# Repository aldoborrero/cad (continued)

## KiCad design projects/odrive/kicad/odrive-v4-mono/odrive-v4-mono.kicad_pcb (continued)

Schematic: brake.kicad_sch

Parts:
C160: 1uF; C_0603_1608Metric
C161, C162, C168, C169, C170: 100nF; C_0603_1608Metric
C163, C164: 2.2uF 100V X7R; C_1210_3225Metric
C165: 100nF 100V X7R; C_0603_1608Metric
C166: 1nF; C_0603_1608Metric
C167, C212: 100nF 16V X7R; C_0603_1608Metric; Tolerance 10%
J13: BRAKE_EXT; TerminalBlock_Phoenix_PC-16-2-ST-10.16mm
Q50, Q51: BSC027N10NS5; Infineon_PG-TSON-8-3; MPN BSC027N10NS5ATMA1
R160: 50R/150R; R_2512_6332Metric
R161, R162: 2.2R; R_0603_1608Metric
R163: 47k; R_0603_1608Metric
R164: 2mR; R_Shunt_Vishay_WSK2512_6332Metric_T2.66mm
R165: 3.3k; R_0603_1608Metric
R166, R167: 10k; R_0603_1608Metric
R168: 1R; R_0603_1608Metric
R212: 10k; R_0603_1608Metric; Tolerance 1%
U50: UCC27517A; SOT-23-5; MPN UCC27517ADBVR
U51: INA181A2; SOT-23-6
U52: TLV3201AIDBVR; SOT-23-5; MPN TLV3201AIDBVR
U53: 74LVC1G3208; SOT-23-6; MPN SN74LVC1G3208DBVR
U54: 74LVC1G32; SOT-23-5
U55: 74LVC1G11; SOT-23-6; MPN SN74LVC1G11DBVR
U58: 74LVC1G14; SOT-23-5; MPN SN74LVC1G14DBVR

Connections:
+12V: C160.1, C161.1, U50.1 (VDD); also elsewhere on the board
/Brake Chopper/BRK_CMD: U54.4, U55.1 (A)
/Brake Chopper/BRK_DRV: R161.1, R162.1, R163.1, U50.5 (OUT)
/Brake Chopper/BRK_G0: Q50.4 (G), R161.2
/Brake Chopper/BRK_G1: Q51.4 (G), R162.2
/Brake Chopper/BRK_GATE: U50.3 (IN+), U55.4 (Y)
/Brake Chopper/BRK_OC_N: R212.1, U52.1 (OUT), U53.6, U55.6 (C)
/Brake Chopper/BRK_RESET_ACTIVE: U53.1, U58.4
/Brake Chopper/BRK_SN: R164.3, U51.4 (-)
/Brake Chopper/BRK_SNUB: C166.1, R168.2
/Brake Chopper/BRK_SP: R164.2, U51.3 (+)
/Brake Chopper/BRK_SRC: C166.2, Q50.1 (S), Q50.2 (S), Q50.3 (S), Q51.1 (S), Q51.2 (S), Q51.3 (S), R163.2, R164.1
/Brake Chopper/BRK_SW: J13.2, Q50.5 (D), Q51.5 (D), R160.2, R168.1
/Brake Chopper/BRK_TH: R165.2, R166.1, U52.3 (+)
AGND: C162.2, C167.2, R166.2, R212.2, U51.2 (GND), U51.5 (REF), U52.2 (GND); also elsewhere on the board
AVCC: C162.1, C167.1, R165.1, U51.6 (V+), U52.5 (VCC); also elsewhere on the board
BRAKE_ISENSE: U51.1, U52.4 (-); also elsewhere on the board
BRAKE_PWM: R167.1, U54.1; also elsewhere on the board
BRK_OK: U53.3, U53.4, U55.3 (B); also elsewhere on the board
DCBUS: C163.1, C164.1, C165.1, J13.1, R160.1; also elsewhere on the board
GND: C168.2, C169.2, C170.2, C212.2, R167.2, U53.2 (GND), U54.3 (GND), U55.2 (GND), U58.3 (GND); also elsewhere on the board
NRST: U58.2; also elsewhere on the board
OV_LATCH: U54.2; also elsewhere on the board
PGND: C160.2, C161.2, C163.2, C164.2, C165.2, R164.4, U50.2 (GND), U50.4 (IN-); also elsewhere on the board
VCC: C168.1, C169.1, C170.1, C212.1, U53.5 (VCC), U54.5 (VCC), U55.5 (VCC), U58.5 (VCC); also elsewhere on the board

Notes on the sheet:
MONO BRAKE FAULT-PRIORITY MEMORY BRK_OK(next) = (BRK_RESET_ACTIVE OR BRK_OK) AND BRK_OC_N. NRST LOW restores permission only while overcurrent is absent. BRK_OC_N LOW always inhibits and removes stored permission. With NRST HIGH, fault recovery alone cannot rearm. U55 independently gates the comman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

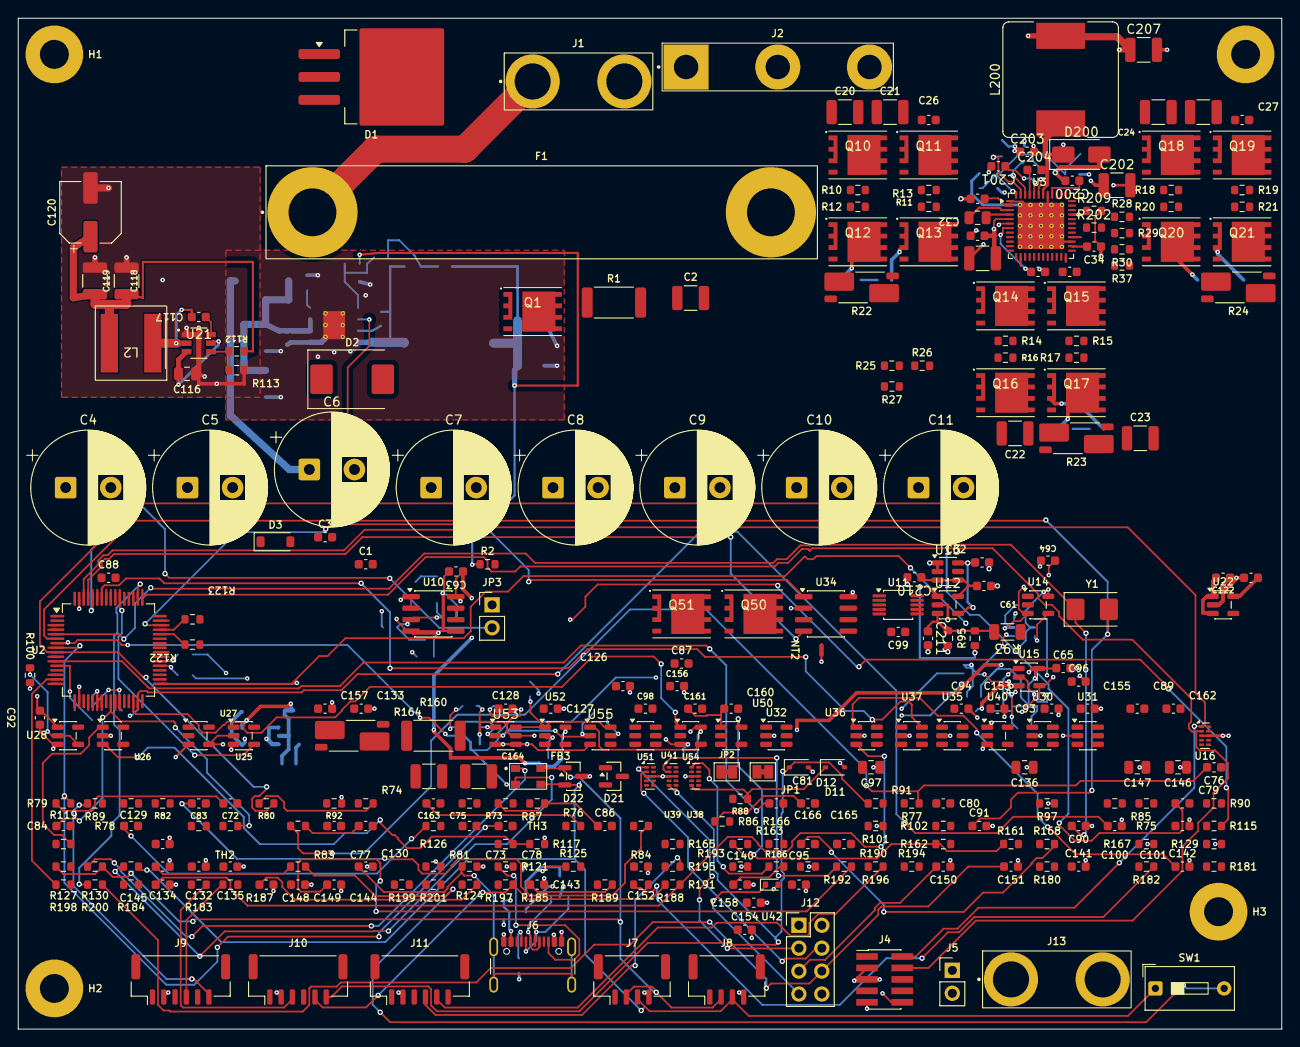
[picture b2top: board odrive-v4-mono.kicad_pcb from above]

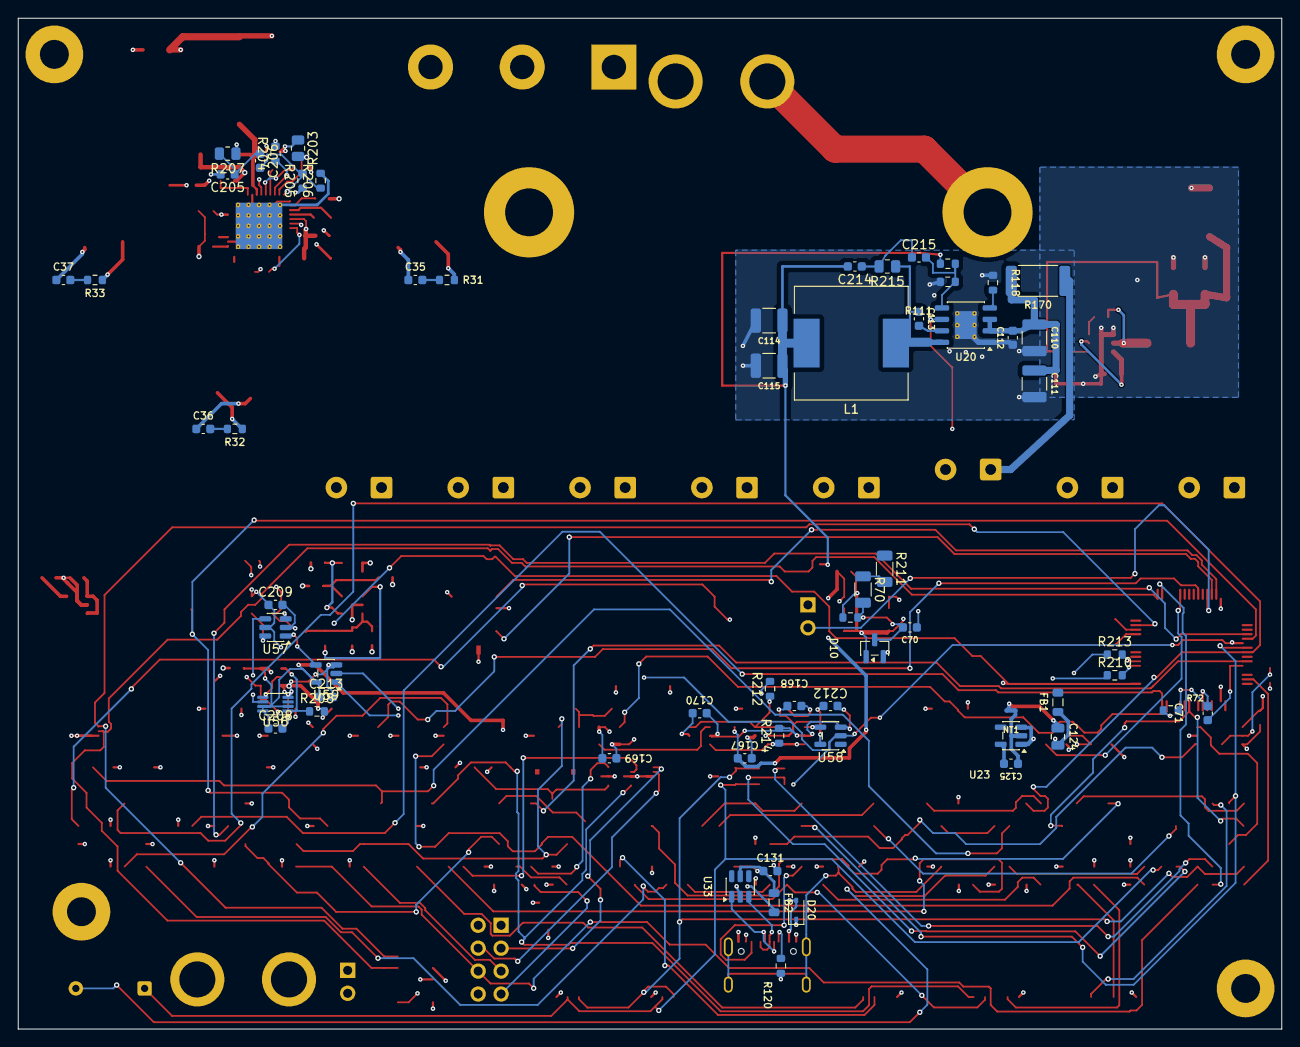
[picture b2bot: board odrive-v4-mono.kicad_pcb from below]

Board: 4 copper layers, 140.0 x 112.0 mm, 360 parts (62 on the bottom side), 206 nets.

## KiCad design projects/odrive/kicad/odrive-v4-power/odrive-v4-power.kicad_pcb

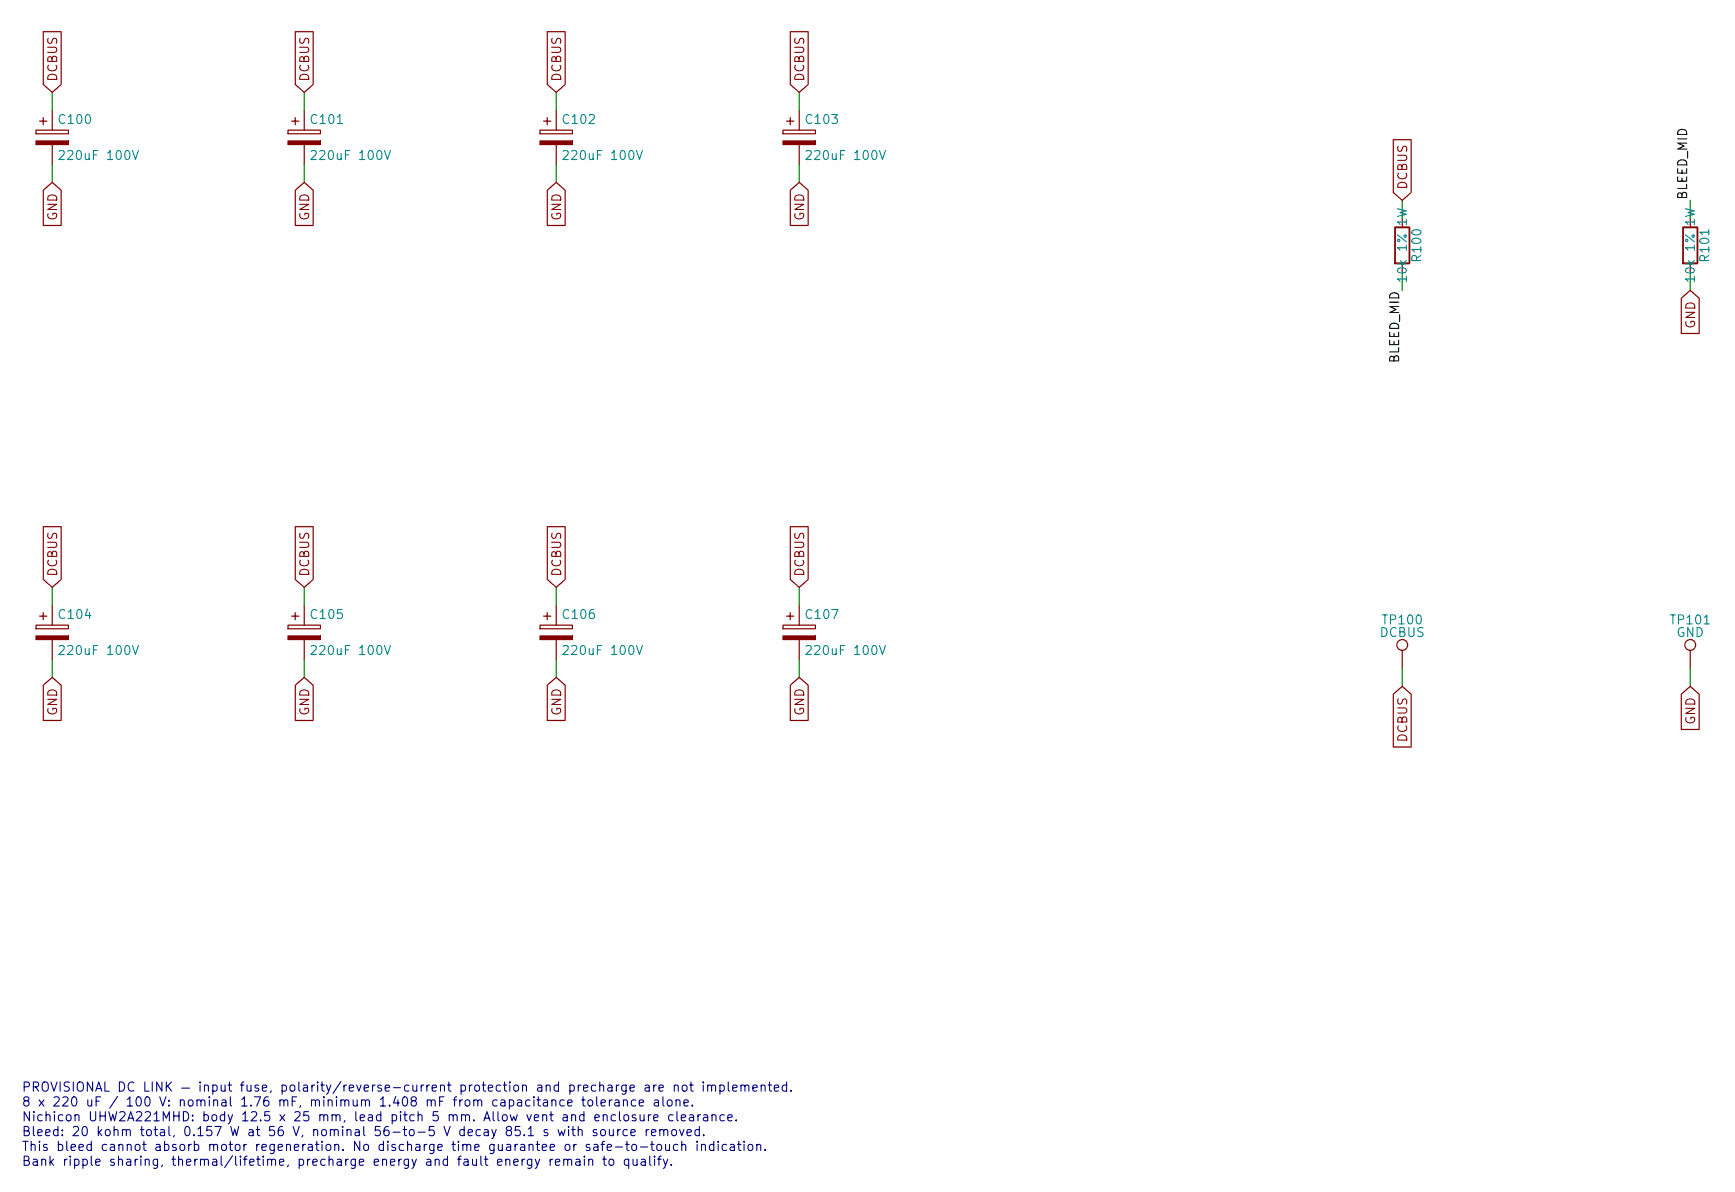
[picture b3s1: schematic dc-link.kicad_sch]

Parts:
C100, C101, C102, C103, C104, C105, C106, C107: 220uF 100V; CP_Radial_D12.5mm_P5.00mm
R100, R101: 10k 1% 1W; R_2512_6332Metric
TP100: DCBUS; TestPoint_Pad_D1.5mm
TP101: GND; TestPoint_Pad_D1.5mm

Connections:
/DC input and link/BLEED_MID: R100.2, R101.1
DCBUS: C100.1, C101.1, C102.1, C103.1, C104.1, C105.1, C106.1, C107.1, R100.1, TP100.1; also elsewhere on the board
GND: C100.2, C101.2, C102.2, C103.2, C104.2, C105.2, C106.2, C107.2, R101.2, TP101.1; also elsewhere on the board

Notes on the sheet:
PROVISIONAL DC LINK — input fuse, polarity/reverse-current protection and precharge are not implemented. 8 x 220 uF / 100 V: nominal 1.76 mF, minimum 1.408 mF from capacitance tolerance alone. Nichicon UHW2A221MHD: body 12.5 x 25 mm, lead pitch 5 mm. Allow vent and enclosure clearance. Bleed: 20 ko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

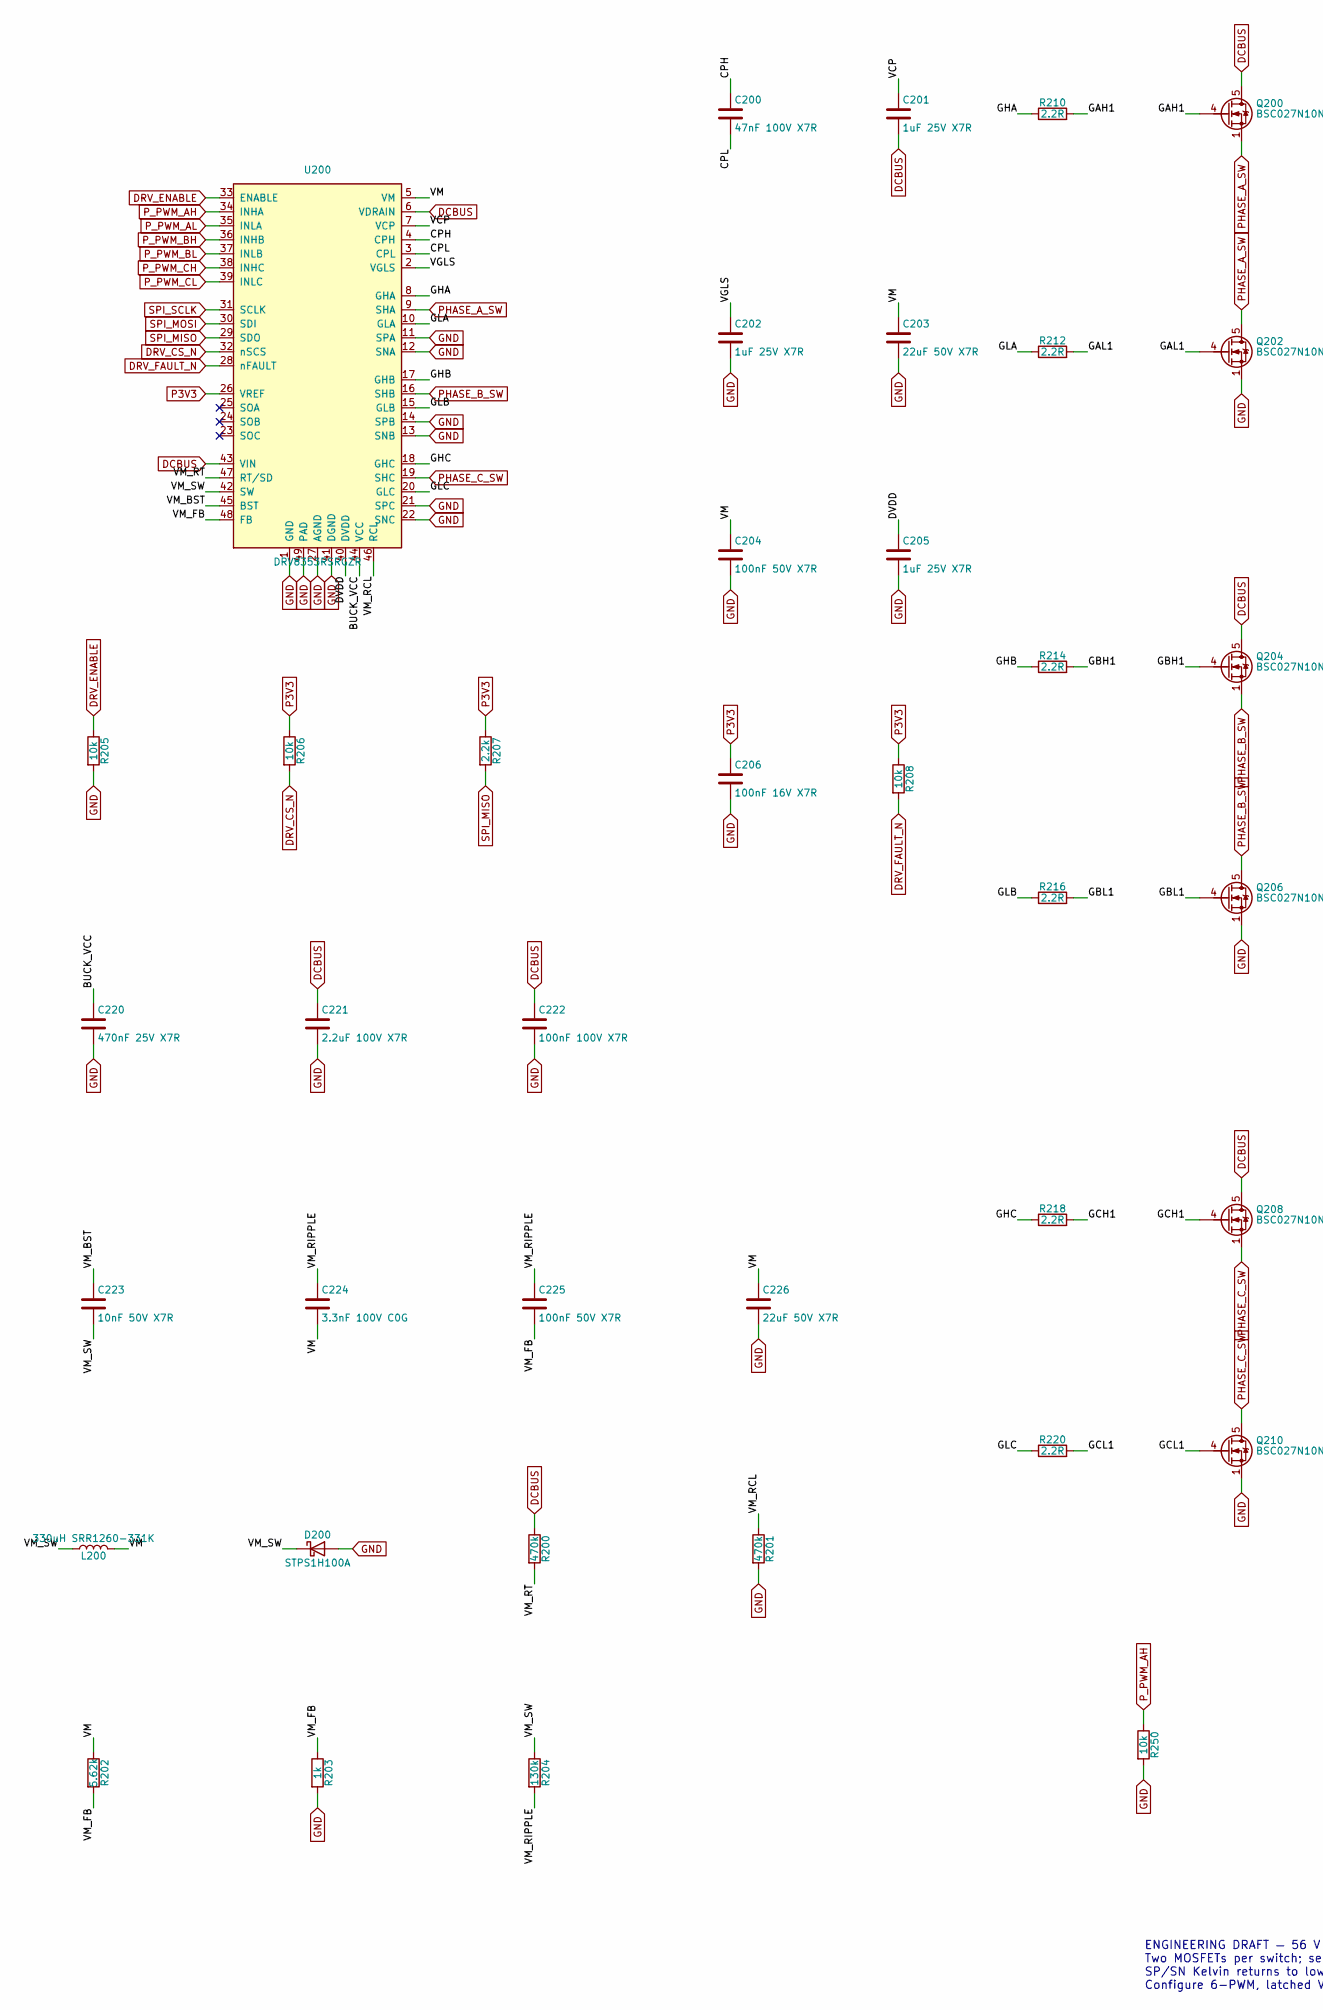
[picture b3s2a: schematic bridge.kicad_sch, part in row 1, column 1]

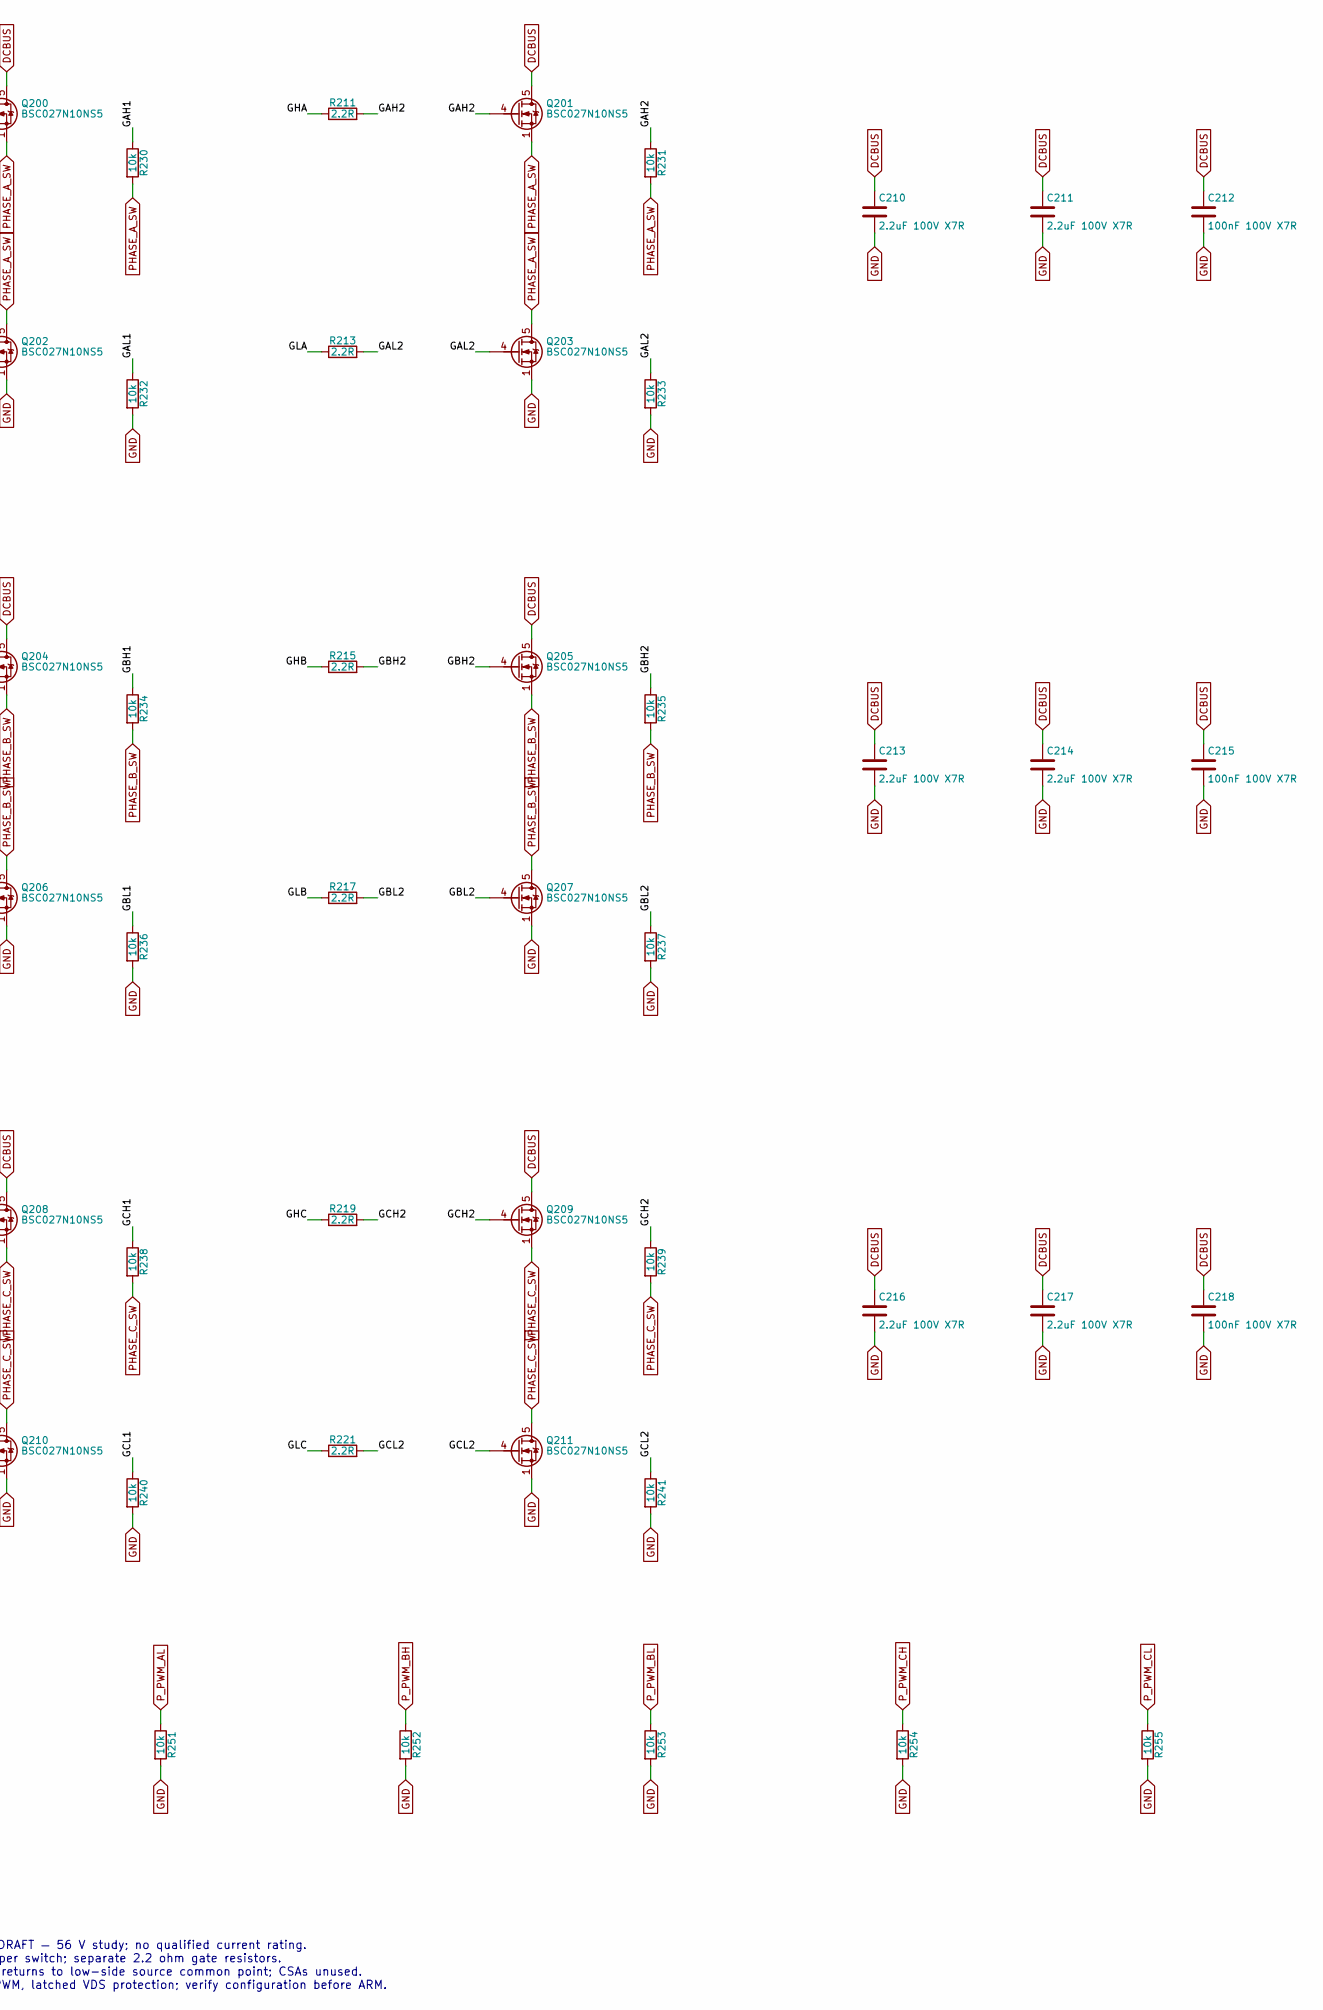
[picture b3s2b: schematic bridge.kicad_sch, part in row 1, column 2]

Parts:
C200: 47nF 100V X7R; C_0805_2012Metric
C201, C202, C205: 1uF 25V X7R; C_0603_1608Metric
C203, C226: 22uF 50V X7R; C_1210_3225Metric
C204, C225: 100nF 50V X7R; C_0603_1608Metric
C206: 100nF 16V X7R; C_0603_1608Metric
C210, C211, C213, C214, C216, C217, C221: 2.2uF 100V X7R; C_1210_3225Metric
C212, C215, C218, C222: 100nF 100V X7R; C_0603_1608Metric
C220: 470nF 25V X7R; C_0603_1608Metric
C223: 10nF 50V X7R; C_0603_1608Metric
C224: 3.3nF 100V C0G; C_0603_1608Metric
D200: STPS1H100A; D_SMA
L200: 330uH SRR1260-331K; L_Bourns_SRR1260
Q200, Q201, Q202, Q203, Q204, Q205, Q206, Q207, Q208, Q209, Q210, Q211: BSC027N10NS5; Infineon_PG-TSON-8-3
R200: 470k; R_0805_2012Metric
R201: 470k; R_0603_1608Metric
R202: 5.62k; R_0603_1608Metric
R203: 1k; R_0603_1608Metric
R204: 130k; R_0805_2012Metric
R205, R206, R208, R230, R231, R232, R233, R234, R235, R236, R237, R238, R239, R240, R241, R250, R251, R252, R253, R254, R255: 10k; R_0603_1608Metric
R207: 2.2k; R_0603_1608Metric
R210, R211, R212, R213, R214, R215, R216, R217, R218, R219, R220, R221: 2.2R; R_0603_1608Metric
U200: DRV8353RSRGZR; QFN-48-1EP_7x7mm_P0.5mm_EP5.15x5.15mm

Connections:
/Three-phase bridge/BUCK_VCC: C220.1, U200.44 (VCC)
/Three-phase bridge/CPH: C200.1, U200.4 (CPH)
/Three-phase bridge/CPL: C200.2, U200.3 (CPL)
/Three-phase bridge/DVDD: C205.1, U200.40 (DVDD)
/Three-phase bridge/GAH1: Q200.4 (G), R210.2, R230.1
/Three-phase bridge/GAH2: Q201.4 (G), R211.2, R231.1
/Three-phase bridge/GAL1: Q202.4 (G), R212.2, R232.1
/Three-phase bridge/GAL2: Q203.4 (G), R213.2, R233.1
/Three-phase bridge/GBH1: Q204.4 (G), R214.2, R234.1
/Three-phase bridge/GBH2: Q205.4 (G), R215.2, R235.1
/Three-phase bridge/GBL1: Q206.4 (G), R216.2, R236.1
/Three-phase bridge/GBL2: Q207.4 (G), R217.2, R237.1
/Three-phase bridge/GCH1: Q208.4 (G), R218.2, R238.1
/Three-phase bridge/GCH2: Q209.4 (G), R219.2, R239.1
/Three-phase bridge/GCL1: Q210.4 (G), R220.2, R240.1
/Three-phase bridge/GCL2: Q211.4 (G), R221.2, R241.1
/Three-phase bridge/GHA: R210.1, R211.1, U200.8 (GHA)
/Three-phase bridge/GHB: R214.1, R215.1, U200.17 (GHB)
/Three-phase bridge/GHC: R218.1, R219.1, U200.18 (GHC)
/Three-phase bridge/GLA: R212.1, R213.1, U200.10 (GLA)
/Three-phase bridge/GLB: R216.1, R217.1, U200.15 (GLB)
/Three-phase bridge/GLC: R220.1, R221.1, U200.20 (GLC)
/Three-phase bridge/VCP: C201.1, U200.7 (VCP)
/Three-phase bridge/VGLS: C202.1, U200.2 (VGLS)
/Three-phase bridge/VM: C203.1, C204.1, C224.2, C226.1, L200.2, R202.1, U200.5 (VM)
/Three-phase bridge/VM_BST: C223.1, U200.45 (BST)
/Three-phase bridge/VM_FB: C225.2, R202.2, R203.1, U200.48 (FB)
/Three-phase bridge/VM_RCL: R201.1, U200.46 (RCL)
/Three-phase bridge/VM_RIPPLE: C224.1, C225.1, R204.2
/Three-phase bridge/VM_RT: R200.2, U200.47 (RT/SD)
/Three-phase bridge/VM_SW: C223.2, D200.1 (K), L200.1, R204.1, U200.42 (SW)
DCBUS: C201.2, C210.1, C211.1, C212.1, C213.1, C214.1, C215.1, C216.1, C217.1, C218.1, C221.1, C222.1, Q200.5 (D), Q201.5 (D), Q204.5 (D), Q205.5 (D), Q208.5 (D), Q209.5 (D), R200.1, U200.6 (VDRAIN), U200.43 (VIN); also elsewhere on the board
DRV_CS_N: R206.2, U200.32 (nSCS); also elsewhere on the board
DRV_ENABLE: R205.1, U200.33 (ENABLE); also elsewhere on the board
DRV_FAULT_N: R208.2, U200.28 (nFAULT); also elsewhere on the board
GND: C202.2, C203.2, C204.2, C205.2, C206.2, C210.2, C211.2, C212.2, C213.2, C214.2, C215.2, C216.2, C217.2, C218.2, C220.2, C221.2, C222.2, C226.2, D200.2 (A), Q202.1 (S), Q202.2 (S), Q202.3 (S), Q203.1 (S), Q203.2 (S), Q203.3 (S), Q206.1 (S), Q206.2 (S), Q206.3 (S), Q207.1 (S), Q207.2 (S), Q207.3 (S), Q210.1 (S), Q210.2 (S), Q210.3 (S), Q211.1 (S), Q211.2 (S), Q211.3 (S), R201.2, R203.2, R205.2, R232.2, R233.2, R236.2, R237.2, R240.2, R241.2, R250.2, R251.2, R252.2, R253.2, R254.2, R255.2, U200.1 (GND), U200.11 (SPA), U200.12 (SNA), U200.13 (SNB), U200.14 (SPB), U200.21 (SPC), U200.22 (SNC), U200.27 (AGND), U200.41 (DGND), U200.49 (PAD); also elsewhere on the board
P3V3: C206.1, R206.1, R207.1, R208.1, U200.26 (VREF); also elsewhere on the board
PHASE_A_SW: Q200.1 (S), Q200.2 (S), Q200.3 (S), Q201.1 (S), Q201.2 (S), Q201.3 (S), Q202.5 (D), Q203.5 (D), R230.2, R231.2, U200.9 (SHA); also elsewhere on the board
PHASE_B_SW: Q204.1 (S), Q204.2 (S), Q204.3 (S), Q205.1 (S), Q205.2 (S), Q205.3 (S), Q206.5 (D), Q207.5 (D), R234.2, R235.2, U200.16 (SHB); also elsewhere on the board
PHASE_C_SW: Q208.1 (S), Q208.2 (S), Q208.3 (S), Q209.1 (S), Q209.2 (S), Q209.3 (S), Q210.5 (D), Q211.5 (D), R238.2, R239.2, U200.19 (SHC); also elsewhere on the board
P_PWM_AH: R250.1, U200.34 (INHA); also elsewhere on the board
P_PWM_AL: R251.1, U200.35 (INLA); also elsewhere on the board
P_PWM_BH: R252.1, U200.36 (INHB); also elsewhere on the board
P_PWM_BL: R253.1, U200.37 (INLB); also elsewhere on the board
P_PWM_CH: R254.1, U200.38 (INHC); also elsewhere on the board
P_PWM_CL: R255.1, U200.39 (INLC); also elsewhere on the board
SPI_MISO: R207.2, U200.29 (SDO); also elsewhere on the board
SPI_MOSI: U200.30 (SDI); also elsewhere on the board
SPI_SCLK: U200.31 (SCLK); also elsewhere on the board

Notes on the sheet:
ENGINEERING DRAFT — 56 V study; no qualified current rating. Two MOSFETs per switch; separate 2.2 ohm gate resistors. SP/SN Kelvin returns to low-side source common point; CSAs unused. Configure 6-PWM, latched VDS protection; verify configuration before ARM.

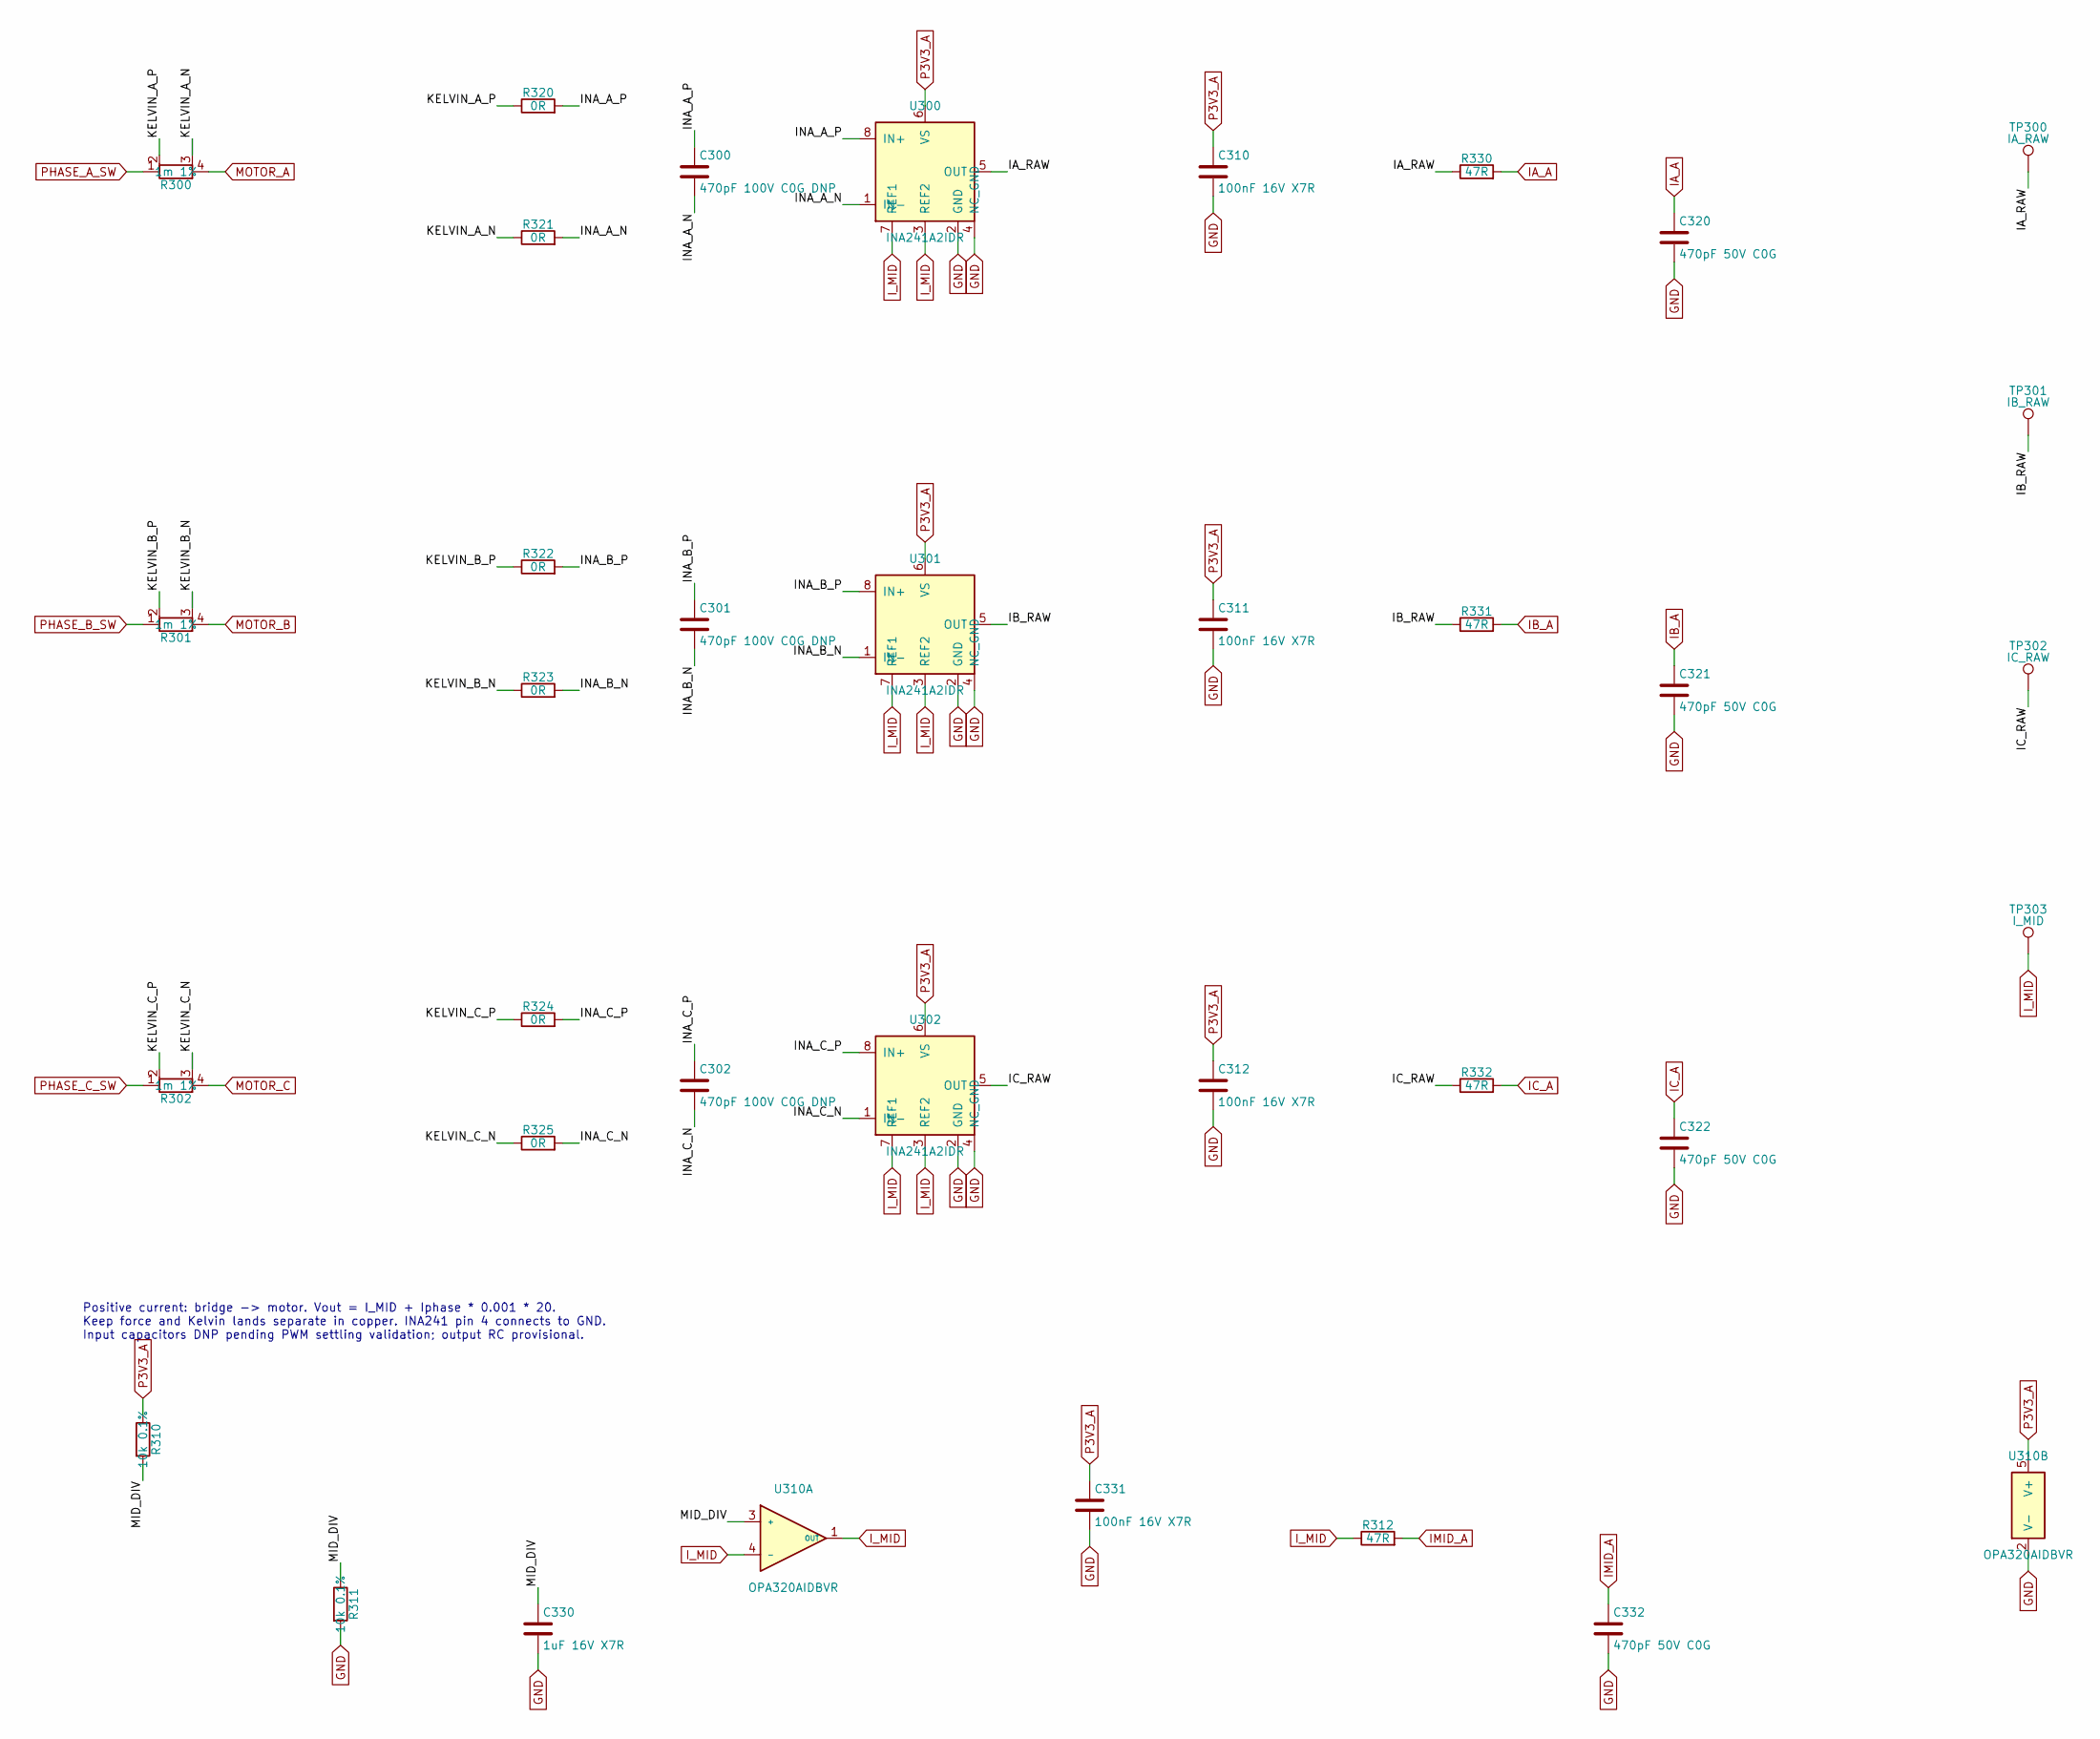
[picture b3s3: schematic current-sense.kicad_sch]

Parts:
C300, C301, C302: 470pF 100V C0G DNP; C_0603_1608Metric
C310, C311, C312, C331: 100nF 16V X7R; C_0603_1608Metric
C320, C321, C322, C332: 470pF 50V C0G; C_0603_1608Metric
C330: 1uF 16V X7R; C_0603_1608Metric
R300, R301, R302: 1m 1%; Bourns_CSS4J-4026_Kelvin
R310, R311: 10k 0.1%; R_0603_1608Metric
R312, R330, R331, R332: 47R; R_0603_1608Metric
R320, R321, R322, R323, R324, R325: 0R; R_0603_1608Metric
TP300: IA_RAW; TestPoint_Pad_D1.0mm
TP301: IB_RAW; TestPoint_Pad_D1.0mm
TP302: IC_RAW; TestPoint_Pad_D1.0mm
TP303: I_MID; TestPoint_Pad_D1.0mm
U300, U301, U302: INA241A2IDR; SOIC-8_3.9x4.9mm_P1.27mm
U310: OPA320AIDBVR; SOT-23-5

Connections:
/Phase-current acquisition/IA_RAW: R330.1, TP300.1, U300.5 (OUT)
/Phase-current acquisition/IB_RAW: R331.1, TP301.1, U301.5 (OUT)
/Phase-current acquisition/IC_RAW: R332.1, TP302.1, U302.5 (OUT)
/Phase-current acquisition/INA_A_N: C300.2, R321.2, U300.1 (IN-)
/Phase-current acquisition/INA_A_P: C300.1, R320.2, U300.8 (IN+)
/Phase-current acquisition/INA_B_N: C301.2, R323.2, U301.1 (IN-)
/Phase-current acquisition/INA_B_P: C301.1, R322.2, U301.8 (IN+)
/Phase-current acquisition/INA_C_N: C302.2, R325.2, U302.1 (IN-)
/Phase-current acquisition/INA_C_P: C302.1, R324.2, U302.8 (IN+)
/Phase-current acquisition/KELVIN_A_N: R300.3, R321.1
/Phase-current acquisition/KELVIN_A_P: R300.2, R320.1
/Phase-current acquisition/KELVIN_B_N: R301.3, R323.1
/Phase-current acquisition/KELVIN_B_P: R301.2, R322.1
/Phase-current acquisition/KELVIN_C_N: R302.3, R325.1
/Phase-current acquisition/KELVIN_C_P: R302.2, R324.1
/Phase-current acquisition/MID_DIV: C330.1, R310.2, R311.1, U310.3 (+)
GND: C310.2, C311.2, C312.2, C320.2, C321.2, C322.2, C330.2, C331.2, C332.2, R311.2, U300.2 (GND), U300.4 (NC_GND), U301.2 (GND), U301.4 (NC_GND), U302.2 (GND), U302.4 (NC_GND), U310.2 (V-); also elsewhere on the board
IA_A: C320.1, R330.2; also elsewhere on the board
IB_A: C321.1, R331.2; also elsewhere on the board
IC_A: C322.1, R332.2; also elsewhere on the board
IMID_A: C332.1, R312.2; also elsewhere on the board
I_MID: R312.1, TP303.1, U300.3 (REF2), U300.7 (REF1), U301.3 (REF2), U301.7 (REF1), U302.3 (REF2), U302.7 (REF1), U310.1 (OUT), U310.4 (-)
MOTOR_A: R300.4
MOTOR_B: R301.4
MOTOR_C: R302.4
P3V3_A: C310.1, C311.1, C312.1, C331.1, R310.1, U300.6 (VS), U301.6 (VS), U302.6 (VS), U310.5 (V+); also elsewhere on the board
PHASE_A_SW: R300.1; also elsewhere on the board
PHASE_B_SW: R301.1; also elsewhere on the board
PHASE_C_SW: R302.1; also elsewhere on the board

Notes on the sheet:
Positive current: bridge -> motor. Vout = I_MID + Iphase * 0.001 * 20. Keep force and Kelvin lands separate in copper. INA241 pin 4 connects to GND. Input capacitors DNP pending PWM settling validation; output RC provisional.
